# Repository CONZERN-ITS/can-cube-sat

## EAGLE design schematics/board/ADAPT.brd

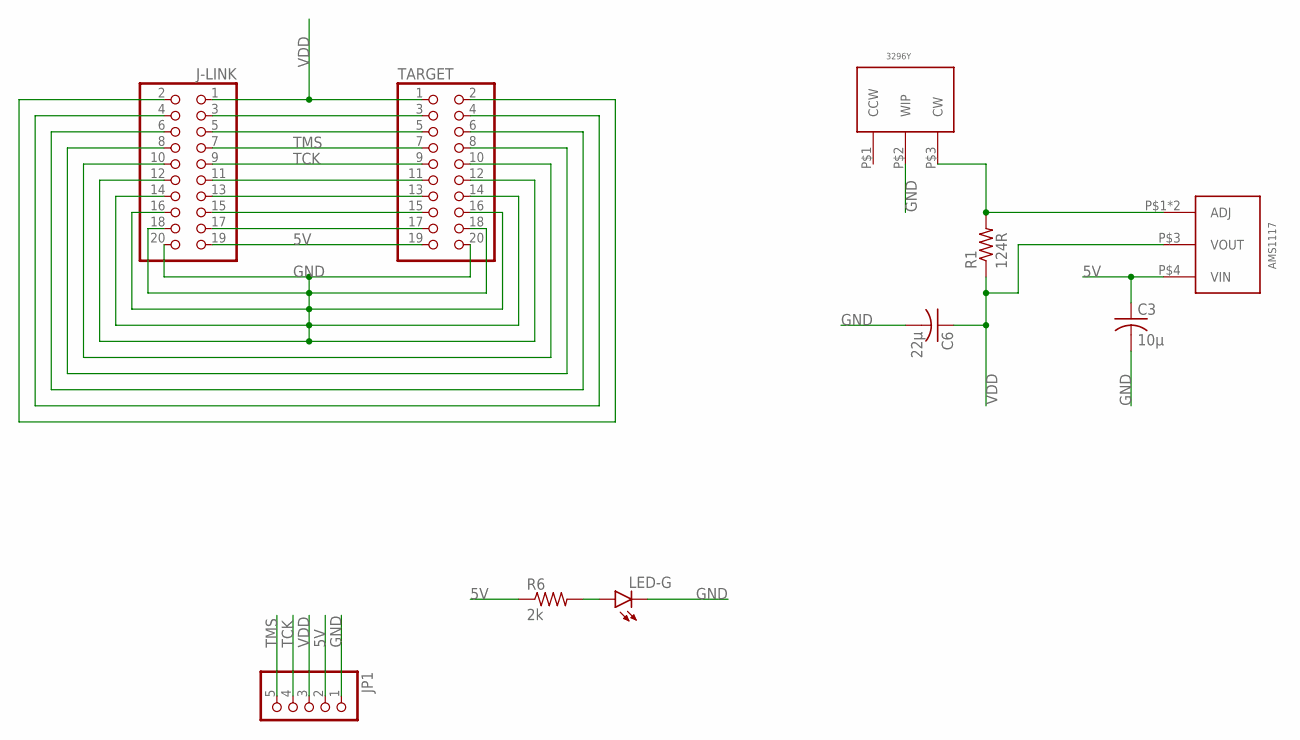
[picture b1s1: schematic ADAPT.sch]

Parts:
3296Y: 3296Y
AMS1117: AMS1117
C3: 10µ; C1206
C6: 22µ; C1206
J-LINK: PINHD-2X10; 2X10
JP1: PINHD-1X5; 1X05
LED-G: LEDCHIPLED_0603; CHIPLED_0603
R1: 124R; R0805
R6: 2k; R0603
TARGET: PINHD-2X10; 2X10

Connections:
5V: AMS1117.P$4 (VIN), C3.1, J-LINK.19, JP1.2, R6.1, TARGET.19
GND: 3296Y.P$2 (WIP), C3.2, C6.2, J-LINK.12, J-LINK.14, J-LINK.16, J-LINK.18, J-LINK.20, JP1.1, LED-G.C, TARGET.12, TARGET.14, TARGET.16, TARGET.18, TARGET.20
unnamed: J-LINK.3, TARGET.3
unnamed: J-LINK.5, TARGET.5
unnamed: 3296Y.P$3 (CW), AMS1117.P$1 (ADJ), AMS1117.P$2 (ADJ), R1.2
unnamed: J-LINK.11, TARGET.11
unnamed: J-LINK.13, TARGET.13
unnamed: J-LINK.15, TARGET.15
unnamed: J-LINK.17, TARGET.17
unnamed: J-LINK.10, TARGET.10
unnamed: J-LINK.8, TARGET.8
unnamed: J-LINK.6, TARGET.6
unnamed: J-LINK.4, TARGET.4
unnamed: J-LINK.2, TARGET.2
unnamed: LED-G.A, R6.2
TCK: J-LINK.9, JP1.4, TARGET.9
TMS: J-LINK.7, JP1.5, TARGET.7
VDD: AMS1117.P$3 (VOUT), C6.1, J-LINK.1, JP1.3, R1.1, TARGET.1

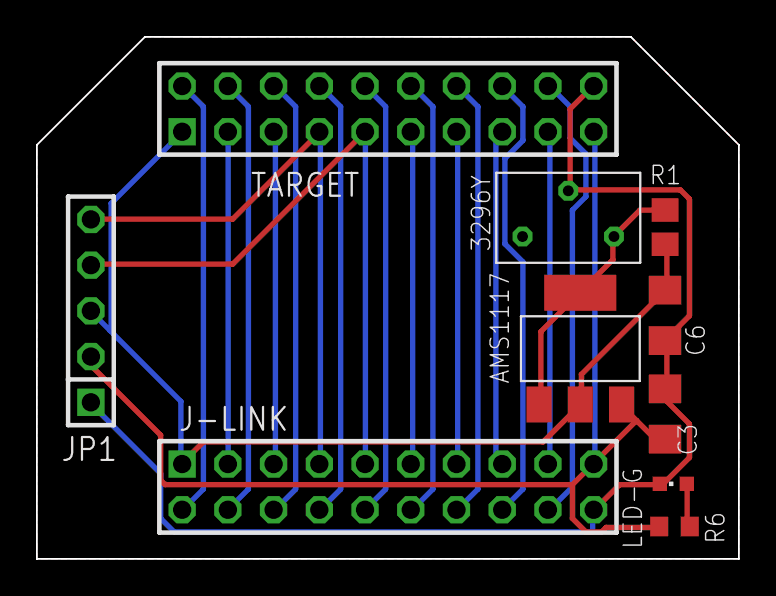
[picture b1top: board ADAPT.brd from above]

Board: 2 copper layers, 39.0 x 29.0 mm, 10 parts (0 on the bottom side), 18 nets.

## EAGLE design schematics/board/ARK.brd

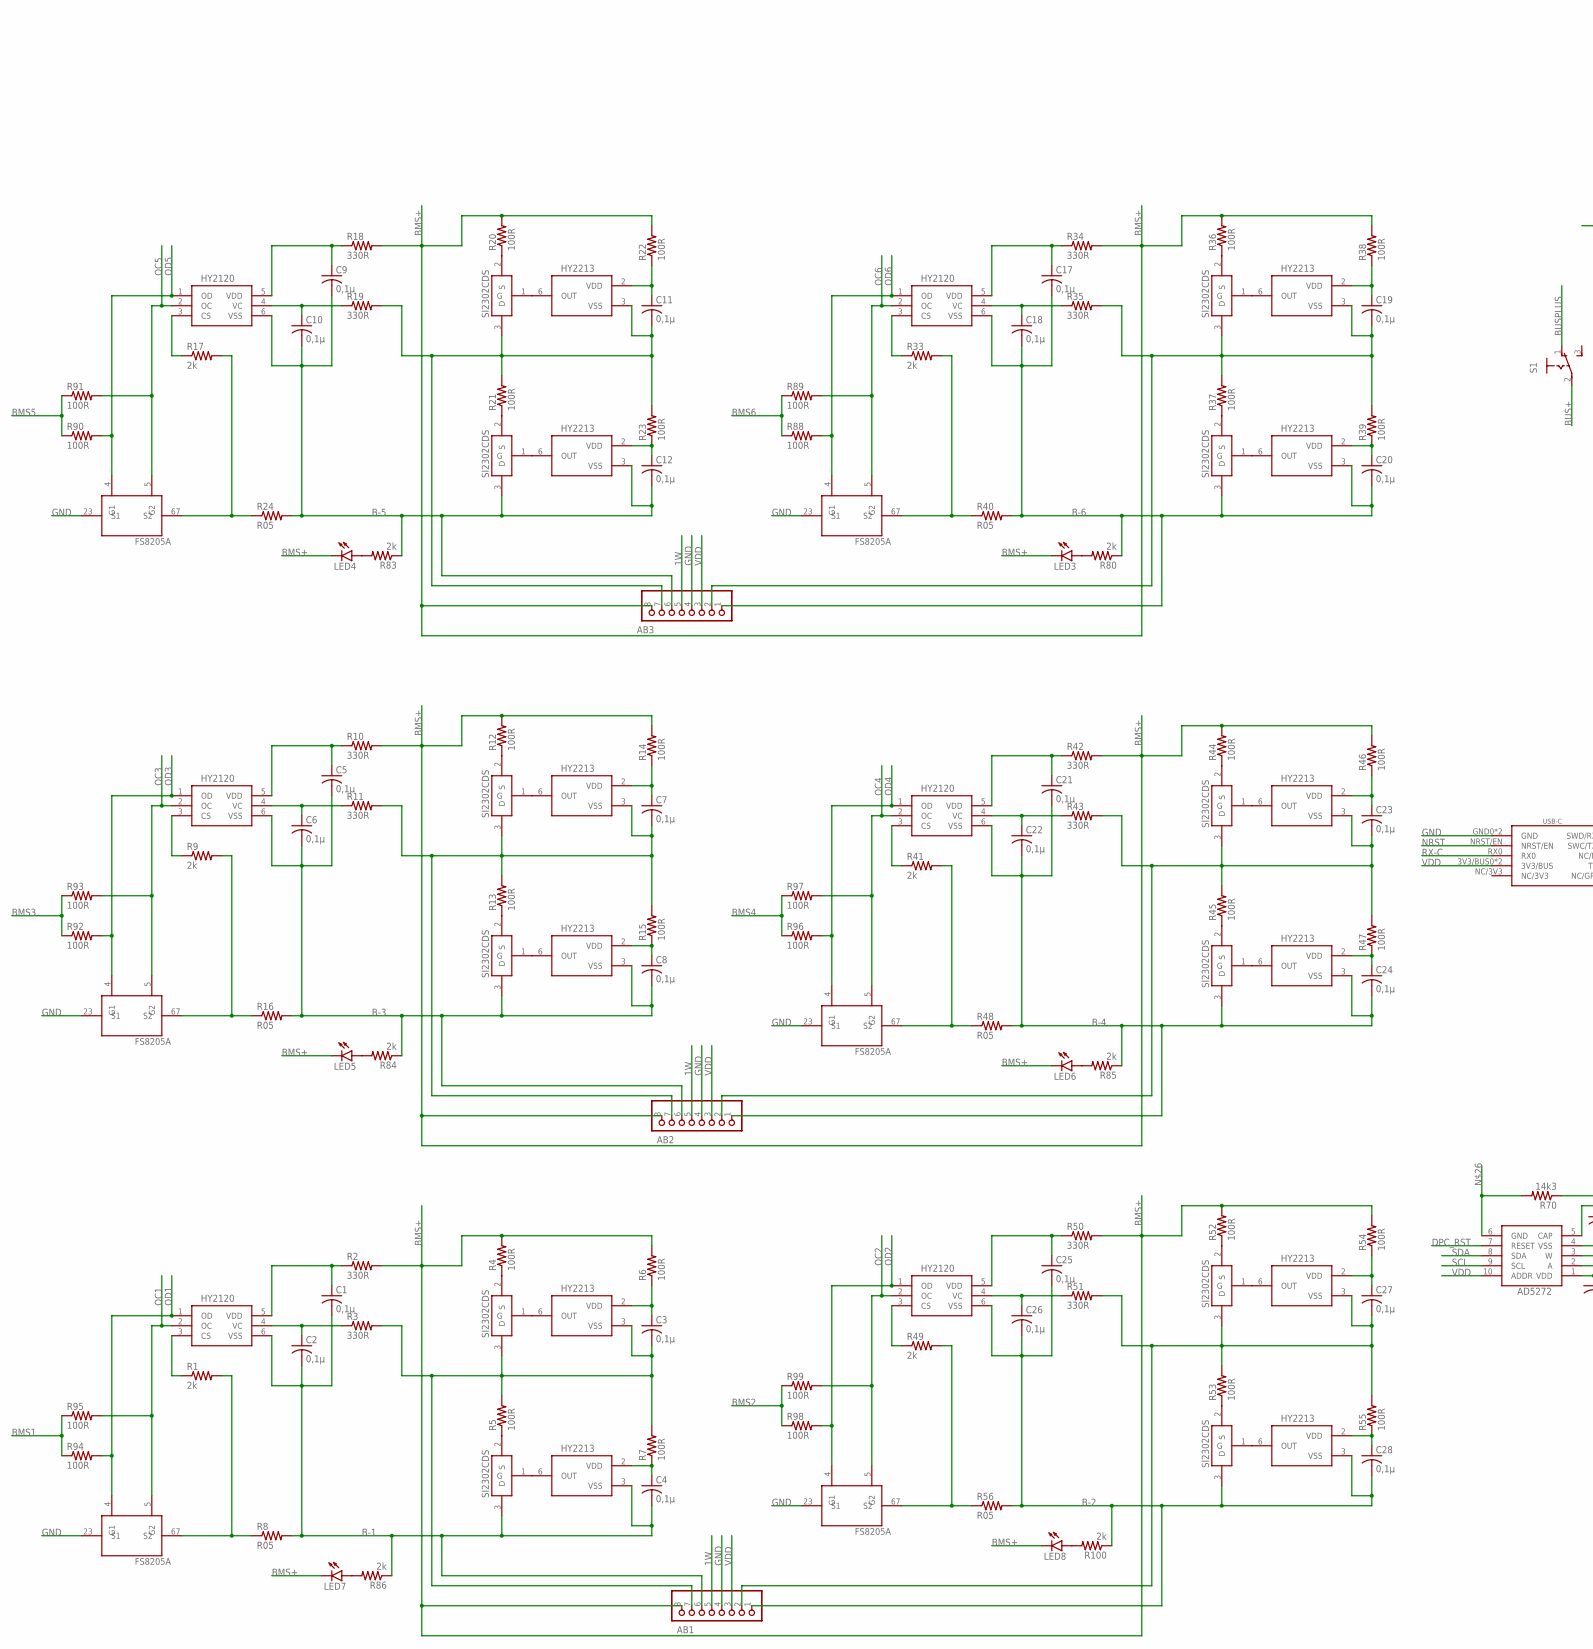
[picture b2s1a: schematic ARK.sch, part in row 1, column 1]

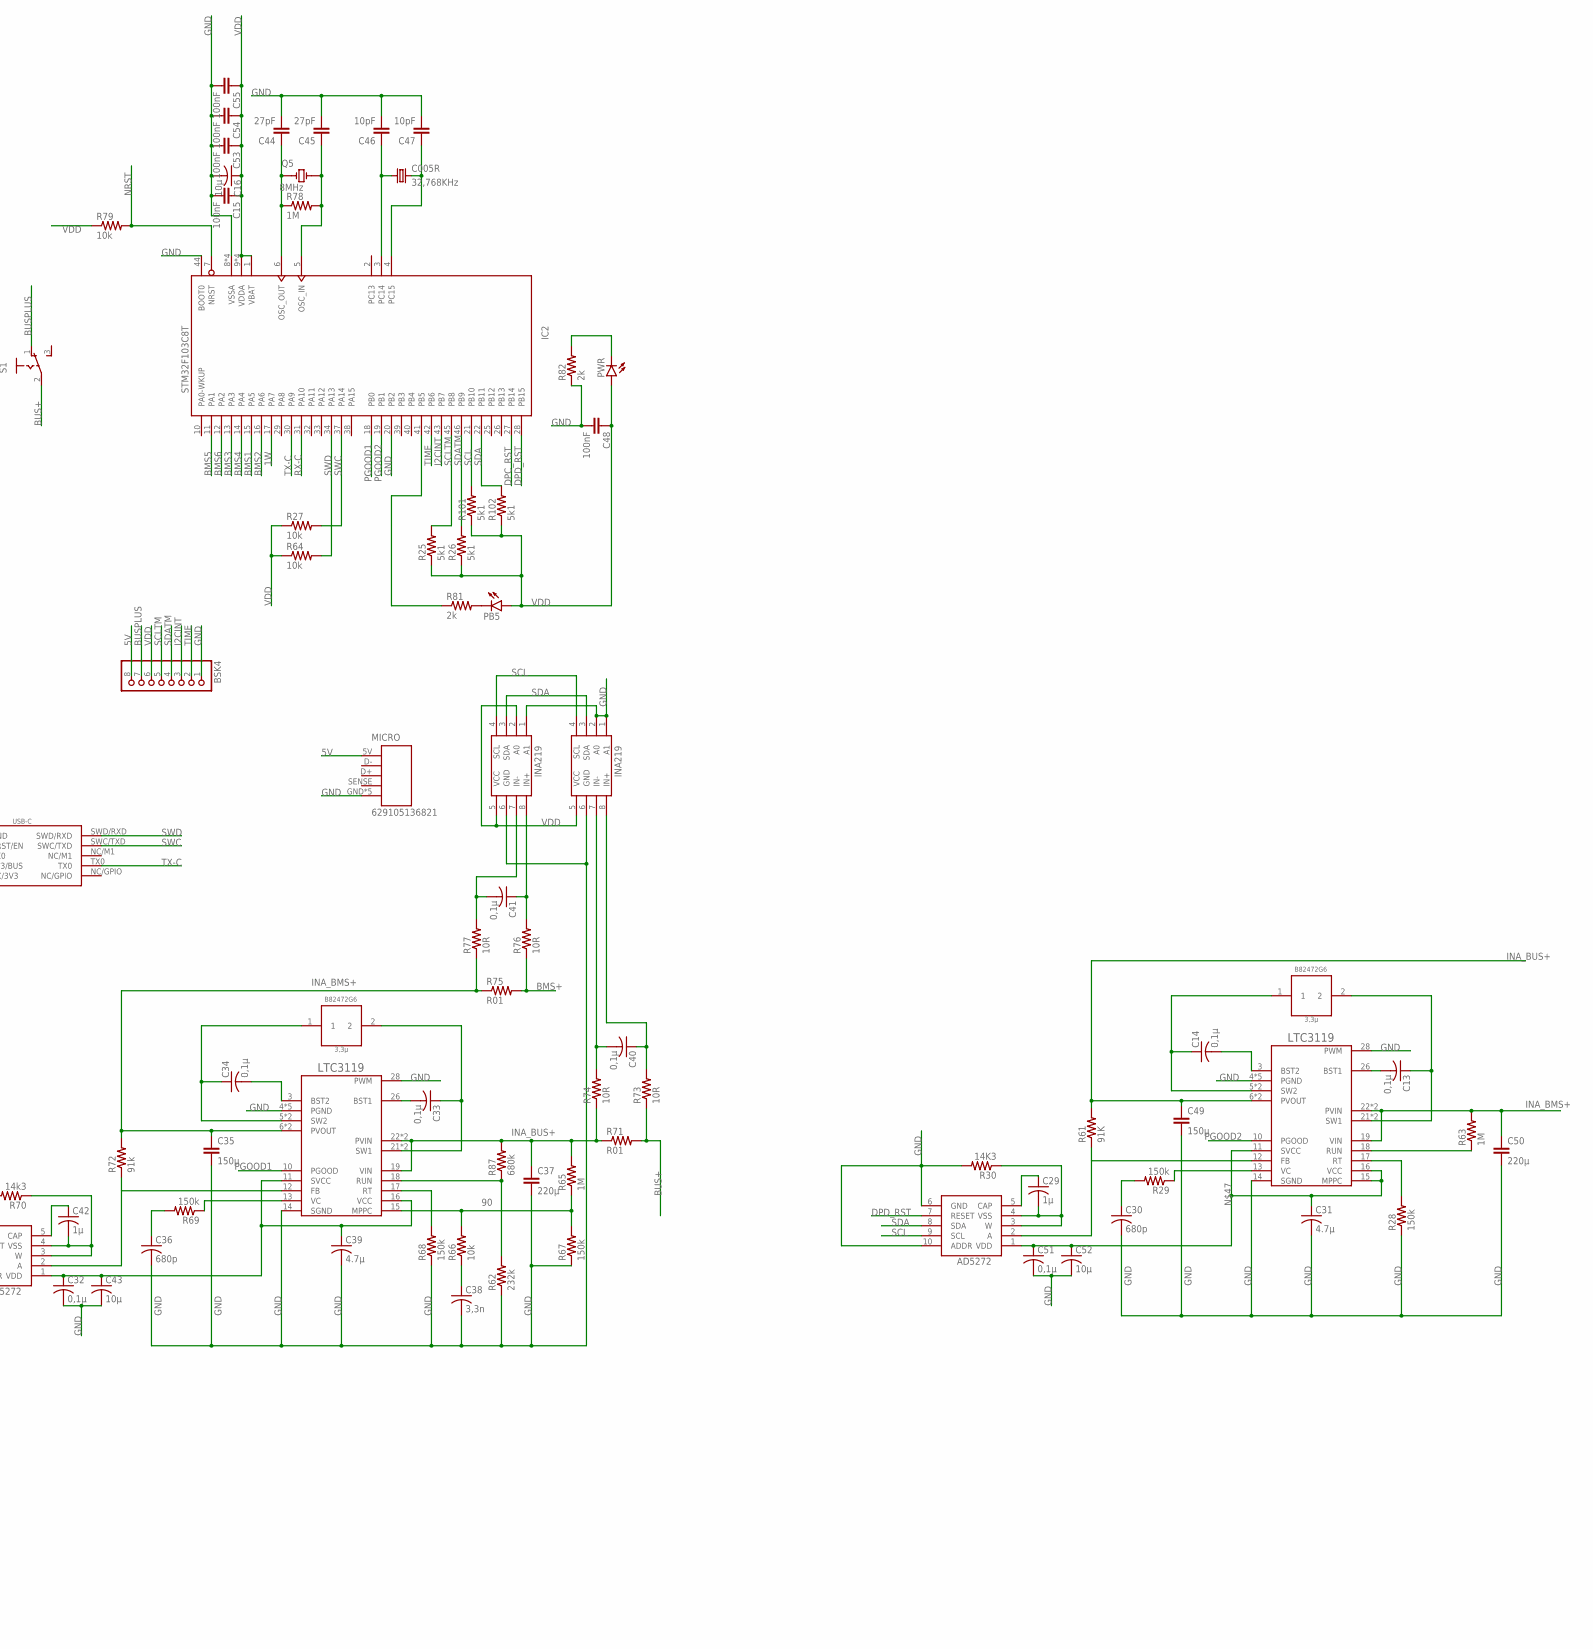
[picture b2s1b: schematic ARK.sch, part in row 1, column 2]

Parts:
3,3µH, 3,3µH1: 3,3µ; B82472G6
AB1, AB2, AB3: PINHD-1X8; 1X08
AD5272#2: AD5272
BSK4: PINHD-1X8; 1X08
C1, C2, C3, C4, C5, C6, C7, C8, C9, C10, C11, C12, C13, C14, C17, C18, C19, C20, C21, C22, C23, C24, C25, C26, C27, C28, C32, C33, C34, C40, C41, C51: 0,1µ; C0603
C005R: 32,768KHz; C005R
C15, C48, C53, C54, C55: 100nF; C0603
C16, C43, C52: 10µ; C1206
C29, C42: 1µ; C0603
C30, C36: 680p; C0603
C31, C39: 4.7µ; C1206
C35, C49: 150µ; ECAP150
C37, C50: 220µ; ECAP220
C38: 3,3n; C0603
C44, C45: 27pF; C0603
C46, C47: 10pF; C0603
IC2: STM32F103C8T; LQFP48
INA219#1: INA219AID
LED3, LED4, LED5, LED6, LED7, LED8: LEDCHIPLED_0603; CHIPLED_0603
MICRO: 629105136821
PB5: LEDCHIPLED_0603; CHIPLED_0603
PWR: LEDCHIPLED_0603; CHIPLED_0603
Q5: 8MHz; XTAL_9C-8.000MEEJ-T
R1, R9, R17, R33, R41, R49, R80, R81, R82, R83, R84, R85, R86, R100: 2k; R0603
R2, R3, R10, R11, R18, R19, R34, R35, R42, R43, R50, R51: 330R; R0603
R4, R5, R6, R7, R12, R13, R14, R15, R20, R21, R22, R23, R36, R37, R38, R39, R44, R45, R46, R47, R52, R53, R54, R55, R88, R89, R90, R91, R92, R93, R94, R95, R96, R97, R98, R99: 100R; R0603
R8, R16, R24, R40, R48, R56: R05; R2512
R25, R26, R101, R102: 5k1; R0603
R27, R64, R66, R79: 10k; R0603
R28, R29, R67, R68, R69: 150k; R0603
R30: 14K3; R0603
R61: 91K; R0603
R62: 232k; R0603
R63, R65, R78: 1M; R0603
R70: 14k3; R0603
R71, R75: R01; R2512
R72: 91k; R0603
R73, R74, R76, R77: 10R; R0603
R87: 680k; R0603
S1: UNICS-SWITCH
U$1, U$8, U$15, U$24, U$25, U$26: FS8205A-
U$3, U$10, U$17, U$31, U$38, U$45: HY2120
U$4, U$5, U$11, U$12, U$18, U$19, U$32, U$33, U$39, U$40, U$46, U$47: HY2213
U$6, U$7, U$13, U$14, U$20, U$21, U$34, U$35, U$41, U$42, U$48, U$49: SI2302CDS
U$16, U$59: LTC3119
U$23: USB-C
U$57: INA219AID
U$60: AD5272

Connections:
1W: AB1.5, AB2.5, AB3.5, IC2.17 (PA7)
5V: BSK4.8, MICRO.5V (1)
90: R65.1, R66.2, R67.2, U$59.15 (MPPC)
B-1: AB1.6, C1.2, C2.2, C4.2, R8.2, R86.1, U$3.6 (VSS), U$5.3 (VSS), U$7.3 (D)
B-2: AB1.1, C25.2, C26.2, C28.2, R56.2, R100.1, U$45.6 (VSS), U$47.3 (VSS), U$49.3 (D)
B-3: AB2.6, C5.2, C6.2, C8.2, R16.2, R84.1, U$10.6 (VSS), U$12.3 (VSS), U$14.3 (D)
B-4: AB2.1, C21.2, C22.2, C24.2, R48.2, R85.1, U$38.6 (VSS), U$40.3 (VSS), U$42.3 (D)
B-5: AB3.6, C9.2, C10.2, C12.2, R24.2, R83.1, U$17.6 (VSS), U$19.3 (VSS), U$21.3 (D)
B-6: AB3.1, C17.2, C18.2, C20.2, R40.2, R80.1, U$31.6 (VSS), U$33.3 (VSS), U$35.3 (D)
BMS1: IC2.15 (PA5), R94.1, R95.1
BMS2: IC2.16 (PA6), R98.1, R99.1
BMS3: IC2.13 (PA3), R92.1, R93.1
BMS4: IC2.14 (PA4), R96.1, R97.1
BMS5: IC2.11 (PA1), R90.1, R91.1
BMS6: IC2.12 (PA2), R88.1, R89.1
BMS+: AB1.8, AB2.8, AB3.8, LED3.C, LED4.C, LED5.C, LED6.C, LED7.C, LED8.C, R2.2, R4.2, R6.2, R10.2, R12.2, R14.2, R18.2, R20.2, R22.2, R34.2, R36.2, R38.2, R42.2, R44.2, R46.2, R50.2, R52.2, R54.2, R75.2, R76.1
BUS+: R71.2, R73.1, S1.2
BUSPLUS: BSK4.7, S1.1 (O)
DPC_RST: IC2.27 (PB14), U$60.7 (RESET)
DPD_RST: AD5272#2.7 (RESET), IC2.28 (PB15)
GND: AB1.4, AB2.4, AB3.4, AD5272#2.6 (GND), AD5272#2.10 (ADDR), BSK4.1, C15.2, C16.2, C30.2, C31.2, C32.2, C35.P$2 (2), C36.2, C37.P$2 (2), C38.2, C39.2, C42.2, C43.2, C44.2, C45.2, C46.2, C47.2, C48.2, C49.P$2 (2), C50.P$2 (2), C51.2, C52.2, C53.2, C54.2, C55.2, IC2.8 (VSSA), IC2.20 (PB2), IC2.23 (VSSA), IC2.35 (VSSA), IC2.44 (BOOT0), IC2.47 (VSSA), INA219#1.1 (A1), INA219#1.2 (A0), INA219#1.6 (GND), MICRO.GND (5), MICRO.Z1 (5), MICRO.Z2 (5), MICRO.Z3 (5), MICRO.Z4 (5), R28.1, R30.2, R62.1, R67.1, R68.1, R70.1, R82.1, U$1.23 (S1), U$8.23 (S1), U$15.23 (S1), U$16.4 (PGND), U$16.9 (PGND), U$16.14 (SGND), U$16.20 (PGND), U$16.25 (PGND), U$16.28 (PWM), U$16.29 (PGND), U$23.GND0 (GND), U$23.GND1 (GND), U$24.23 (S1), U$25.23 (S1), U$26.23 (S1), U$57.1 (A1), U$57.6 (GND), U$59.4 (PGND), U$59.9 (PGND), U$59.14 (SGND), U$59.20 (PGND), U$59.25 (PGND), U$59.28 (PWM), U$59.29 (PGND), U$60.3 (W), U$60.4 (VSS)
I2CINT: BSK4.3, IC2.43 (PB7)
INA_BMS+: C35.P$1 (1), C50.P$1 (1), R63.2, R72.2, R75.1, R77.1, U$16.19 (VIN), U$16.22 (PVIN), U$16.23 (PVIN), U$59.6 (PVOUT), U$59.7 (PVOUT)
INA_BUS+: C37.P$1 (1), C49.P$1 (1), R61.2, R65.2, R71.1, R74.1, R87.2, U$16.6 (PVOUT), U$16.7 (PVOUT), U$59.19 (VIN), U$59.22 (PVIN), U$59.23 (PVIN)
unnamed: C1.1, R2.1, U$3.5 (VDD)
unnamed: C4.1, R7.1, U$5.2 (VDD)
unnamed: R1.1, U$3.3 (CS)
unnamed: C3.1, R6.1, U$4.2 (VDD)
unnamed: AD5272#2.2 (A), R61.1, U$16.12 (FB)
unnamed: U$4.6 (OUT), U$6.1 (G)
unnamed: R4.1, U$6.2 (S)
unnamed: AB1.7, C3.2, R3.2, R5.2, R7.2, U$4.3 (VSS), U$6.3 (D)
unnamed: U$5.6 (OUT), U$7.1 (G)
unnamed: R5.1, U$7.2 (S)
unnamed: 3,3µH1.2, C13.1, U$16.21 (SW1), U$16.24 (SW1)
unnamed: 3,3µH1.1, C14.1, U$16.5 (SW2), U$16.8 (SW2)
unnamed: R1.2, R8.1, U$26.67 (S2)
unnamed: C2.1, R3.1, U$3.4 (VC)
unnamed: C5.1, R10.1, U$10.5 (VDD)
unnamed: PB5.C, R81.2
unnamed: R9.1, U$10.3 (CS)
unnamed: C7.1, R14.1, U$11.2 (VDD)
unnamed: U$11.6 (OUT), U$13.1 (G)
unnamed: R12.1, U$13.2 (S)
unnamed: U$12.6 (OUT), U$14.1 (G)
unnamed: R13.1, U$14.2 (S)
unnamed: R9.2, R16.1, U$25.67 (S2)
unnamed: R72.1, U$59.12 (FB), U$60.2 (A)
unnamed: R70.2, U$60.6 (GND)
unnamed: C6.1, R11.1, U$10.4 (VC)
unnamed: C8.1, R15.1, U$12.2 (VDD)
unnamed: R28.2, U$16.17 (RT)
unnamed: AB2.7, C7.2, R11.2, R13.2, R15.2, U$11.3 (VSS), U$13.3 (D)
unnamed: C13.2, U$16.26 (BST1)
unnamed: C9.1, R18.1, U$17.5 (VDD)
unnamed: R17.1, U$17.3 (CS)
unnamed: C11.1, R22.1, U$18.2 (VDD)
unnamed: U$18.6 (OUT), U$20.1 (G)
unnamed: R20.1, U$20.2 (S)
unnamed: U$19.6 (OUT), U$21.1 (G)
unnamed: R21.1, U$21.2 (S)
unnamed: R17.2, R24.1, U$24.67 (S2)
unnamed: R29.1, U$16.13 (VC)
unnamed: C30.1, R29.2
unnamed: C10.1, R19.1, U$17.4 (VC)
unnamed: C12.1, R23.1, U$19.2 (VDD)
unnamed: C32.1, C39.1, C43.1, U$59.11 (SVCC), U$59.16 (VCC), U$60.1 (VDD)
unnamed: AB3.7, C11.2, R19.2, R21.2, R23.2, U$18.3 (VSS), U$20.3 (D)
unnamed: AD5272#2.1 (VDD), C31.1, C51.1, C52.1, U$16.11 (SVCC), U$16.15 (MPPC), U$16.16 (VCC)
unnamed: AD5272#2.3 (W), AD5272#2.4 (VSS), C29.2, R30.1
unnamed: AD5272#2.5 (CAP), C29.1
unnamed: C14.2, U$16.3 (BST2)
unnamed: R63.1, U$16.18 (RUN)
unnamed: LED3.A, R80.2
unnamed: R62.2, R87.1, U$59.18 (RUN)
unnamed: LED4.A, R83.2
unnamed: LED5.A, R84.2
unnamed: LED6.A, R85.2
unnamed: LED7.A, R86.2
unnamed: LED8.A, R100.2
unnamed: C17.1, R34.1, U$31.5 (VDD)
unnamed: R33.1, U$31.3 (CS)
unnamed: C19.1, R38.1, U$32.2 (VDD)
unnamed: U$32.6 (OUT), U$34.1 (G)
unnamed: R36.1, U$34.2 (S)
unnamed: U$33.6 (OUT), U$35.1 (G)
unnamed: R37.1, U$35.2 (S)
unnamed: R33.2, R40.1, U$15.67 (S2)
unnamed: C18.1, R35.1, U$31.4 (VC)
unnamed: C20.1, R39.1, U$33.2 (VDD)
unnamed: AB3.2, C19.2, R35.2, R37.2, R39.2, U$32.3 (VSS), U$34.3 (D)
unnamed: C21.1, R42.1, U$38.5 (VDD)
unnamed: R41.1, U$38.3 (CS)
unnamed: C23.1, R46.1, U$39.2 (VDD)
unnamed: U$39.6 (OUT), U$41.1 (G)
unnamed: R44.1, U$41.2 (S)
unnamed: U$40.6 (OUT), U$42.1 (G)
unnamed: R45.1, U$42.2 (S)
unnamed: R41.2, R48.1, U$8.67 (S2)
unnamed: C22.1, R43.1, U$38.4 (VC)
unnamed: C24.1, R47.1, U$40.2 (VDD)
unnamed: AB2.2, C23.2, R43.2, R45.2, R47.2, U$39.3 (VSS), U$41.3 (D)
unnamed: C25.1, R50.1, U$45.5 (VDD)
unnamed: R49.1, U$45.3 (CS)
unnamed: C27.1, R54.1, U$46.2 (VDD)
unnamed: U$46.6 (OUT), U$48.1 (G)
unnamed: R52.1, U$48.2 (S)
unnamed: U$47.6 (OUT), U$49.1 (G)
unnamed: R53.1, U$49.2 (S)
unnamed: R49.2, R56.1, U$1.67 (S2)
unnamed: C26.1, R51.1, U$45.4 (VC)
unnamed: C28.1, R55.1, U$47.2 (VDD)
unnamed: AB1.2, C27.2, R51.2, R53.2, R55.2, U$46.3 (VSS), U$48.3 (D)
unnamed: C34.2, U$59.3 (BST2)
unnamed: 3,3µH.2, C33.1, U$59.21 (SW1), U$59.24 (SW1)
unnamed: 3,3µH.1, C34.1, U$59.5 (SW2), U$59.8 (SW2)
unnamed: C44.1, IC2.6 (OSC_OUT), Q5.1, R78.1
unnamed: R69.1, U$59.13 (VC)
unnamed: C36.1, R69.2
unnamed: C38.1, R66.1
unnamed: C40.2, INA219#1.7 (IN-), R74.2
unnamed: R68.2, U$59.17 (RT)
unnamed: C33.2, U$59.26 (BST1)
unnamed: C45.1, IC2.5 (OSC_IN), Q5.2, R78.2
unnamed: C40.1, INA219#1.8 (IN+), R73.2
unnamed: C005R.P$2 (2), C47.1, IC2.4 (PC15)
unnamed: C41.1, R76.2, U$57.8 (IN+)
unnamed: C41.2, R77.2, U$57.7 (IN-)
unnamed: C005R.P$1 (1), C46.1, IC2.3 (PC14)
unnamed: C42.1, U$60.5 (CAP)
unnamed: PWR.C, R82.2
unnamed: IC2.41 (PB5), R81.1
NRST: IC2.7 (NRST), R79.2, U$23.NRST/EN
OC1: R95.2, U$3.2 (OC), U$26.5 (G2)
OC2: R99.2, U$1.5 (G2), U$45.2 (OC)
OC3: R93.2, U$10.2 (OC), U$25.5 (G2)
OC4: R97.2, U$8.5 (G2), U$38.2 (OC)
OC5: R91.2, U$17.2 (OC), U$24.5 (G2)
OC6: R89.2, U$15.5 (G2), U$31.2 (OC)
OD1: R94.2, U$3.1 (OD), U$26.4 (G1)
OD2: R98.2, U$1.4 (G1), U$45.1 (OD)
OD3: R92.2, U$10.1 (OD), U$25.4 (G1)
OD4: R96.2, U$8.4 (G1), U$38.1 (OD)
OD5: R90.2, U$17.1 (OD), U$24.4 (G1)
OD6: R88.2, U$15.4 (G1), U$31.1 (OD)
PGOOD1: IC2.18 (PB0), U$59.10 (PGOOD)
PGOOD2: IC2.19 (PB1), U$16.10 (PGOOD)
RX-C: IC2.31 (PA10), U$23.RX0
SCL: AD5272#2.9 (SCL), IC2.21 (PB10), INA219#1.4 (SCL), R101.2, U$57.4 (SCL), U$60.9 (SCL)
SCLTM: BSK4.5, IC2.45 (PB8), R25.2
SDA: AD5272#2.8 (SDA), IC2.22 (PB11), INA219#1.3 (SDA), R102.2, U$57.3 (SDA), U$60.8 (SDA)
SDATM: BSK4.4, IC2.46 (PB9), R26.2
SWC: IC2.37 (PA14), R27.2, U$23.SWC/TXD
SWD: IC2.34 (PA13), R64.2, U$23.SWD/RXD
TIME: BSK4.2, IC2.42 (PB6)
TX-C: IC2.30 (PA9), U$23.TX0
VDD: AB1.3, AB2.3, AB3.3, BSK4.6, C15.1, C16.1, C48.1, C53.1, C54.1, C55.1, IC2.1 (VBAT), IC2.9 (VDDA), IC2.24 (VDDA), IC2.36 (VDDA), IC2.48 (VDDA), INA219#1.5 (VCC), PB5.A, PWR.A, R25.1, R26.1, R27.1, R64.1, R79.1, R101.1, R102.1, U$23.3V3/BUS0 (3V3/BUS), U$23.3V3/BUS1 (3V3/BUS), U$57.2 (A0), U$57.5 (VCC), U$60.10 (ADDR)

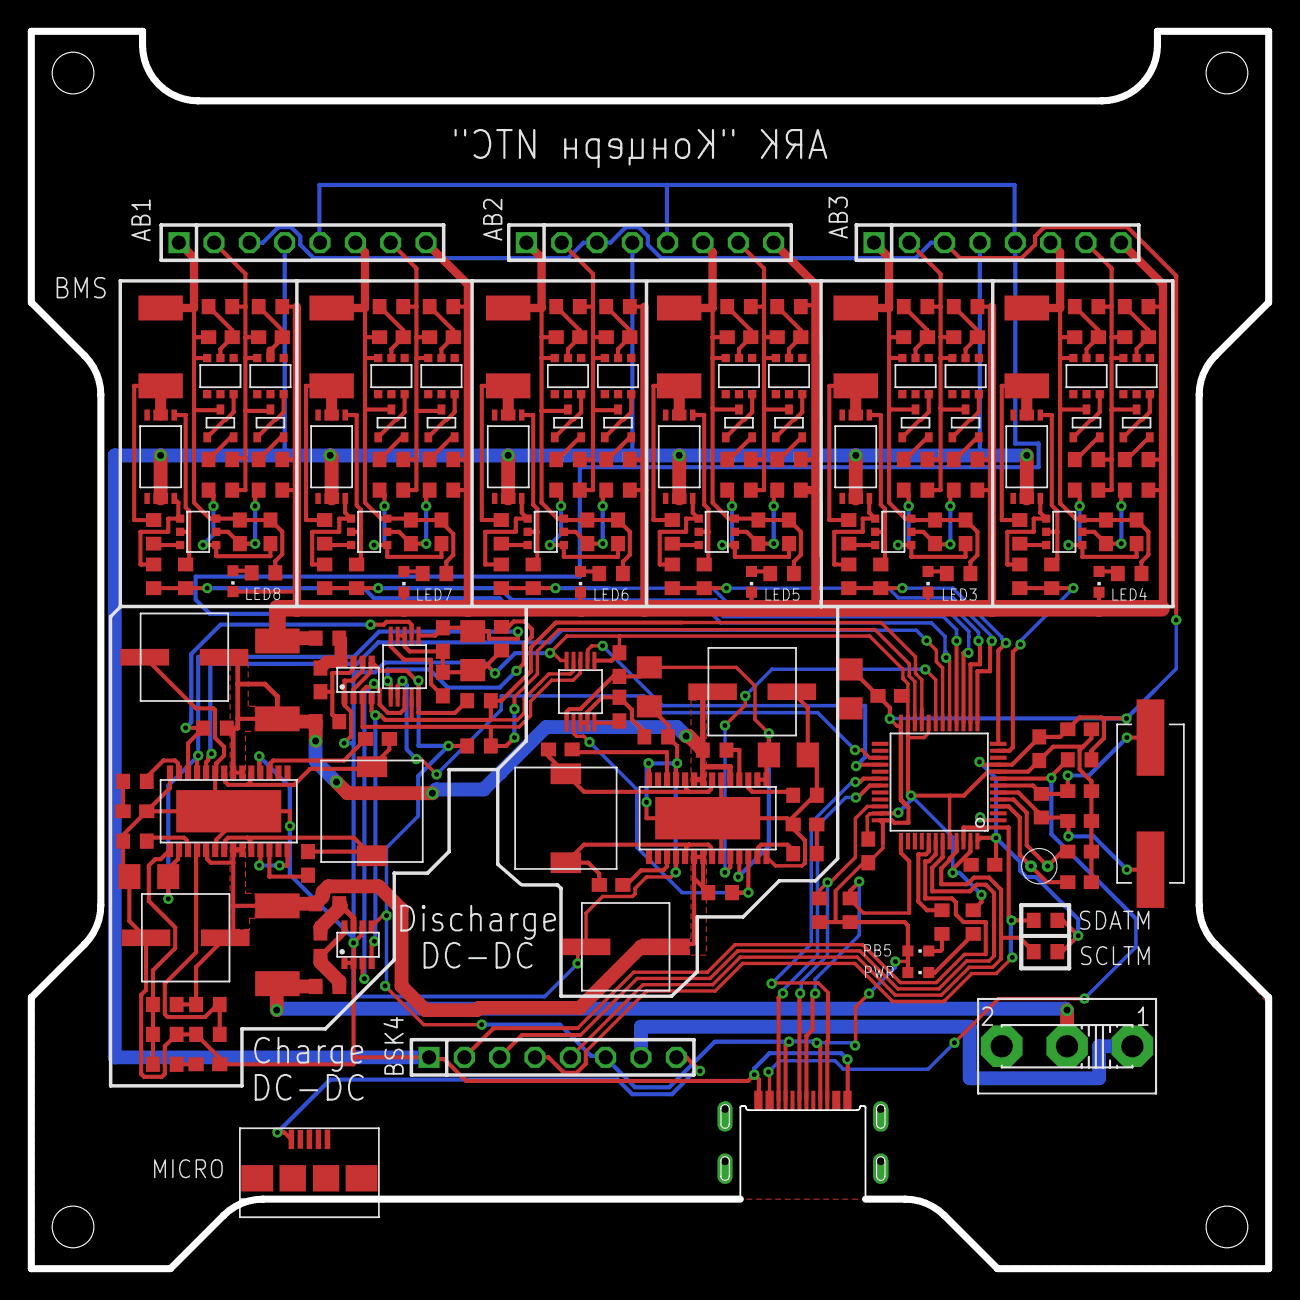
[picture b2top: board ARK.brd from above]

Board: 2 copper layers, 89.0 x 89.0 mm, 213 parts (0 on the bottom side), 157 nets.

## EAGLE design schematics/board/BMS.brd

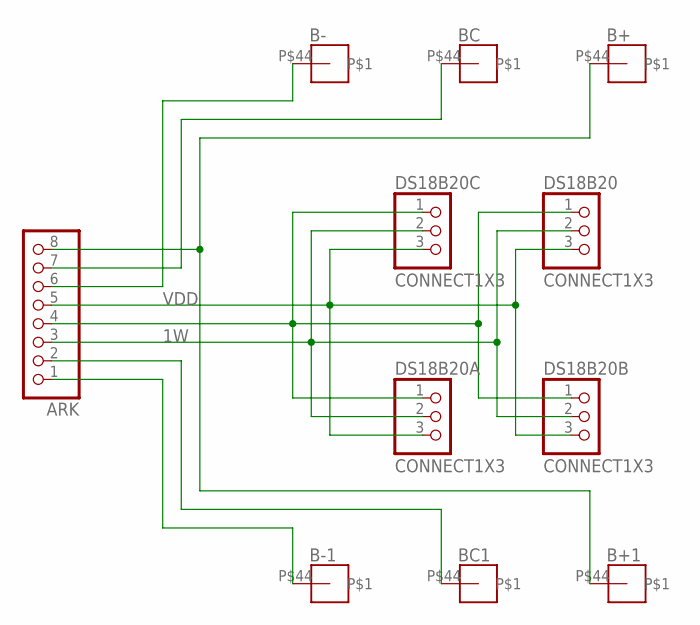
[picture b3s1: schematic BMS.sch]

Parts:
ARK: PINHD-1X8; 1X08
B+, B+1: DRILLBAT5
B-, B-1: DRILLBAT5
BC, BC1: DRILLBAT5
DS18B20, DS18B20A, DS18B20B, DS18B20C: CONNECT1X3

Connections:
1W: ARK.3, DS18B20.2, DS18B20A.2, DS18B20B.2, DS18B20C.2
BMS+: ARK.8, B+.P$44, B+1.P$44
unnamed: ARK.4, DS18B20.1, DS18B20A.1, DS18B20B.1, DS18B20C.1
unnamed: ARK.6, B-.P$44
unnamed: ARK.1, B-1.P$44
unnamed: ARK.7, BC.P$44
unnamed: ARK.2, BC1.P$44
VDD: ARK.5, DS18B20.3, DS18B20A.3, DS18B20B.3, DS18B20C.3

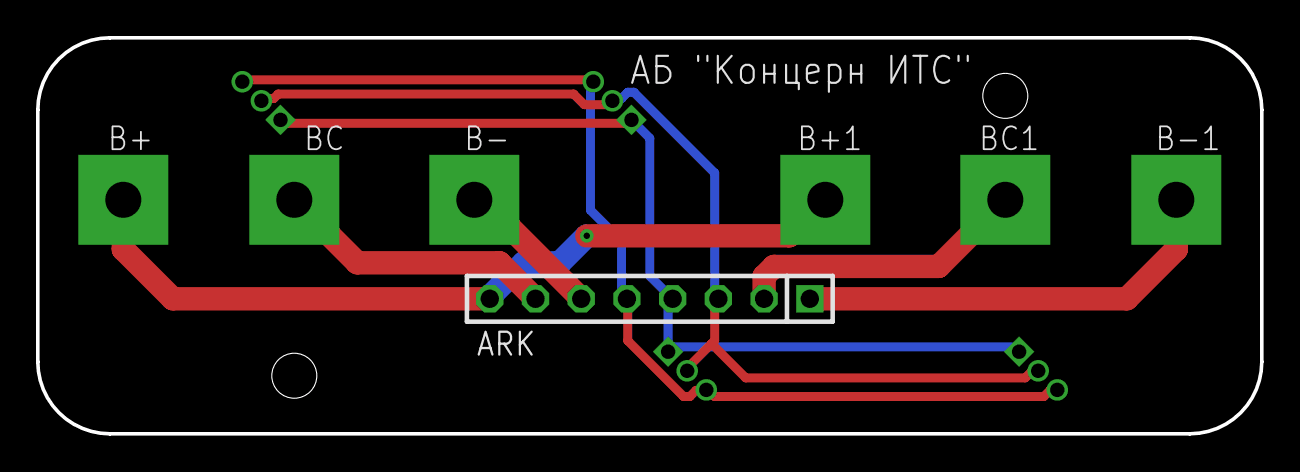
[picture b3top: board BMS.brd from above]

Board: 2 copper layers, 68.0 x 22.0 mm, 11 parts (0 on the bottom side), 8 nets.

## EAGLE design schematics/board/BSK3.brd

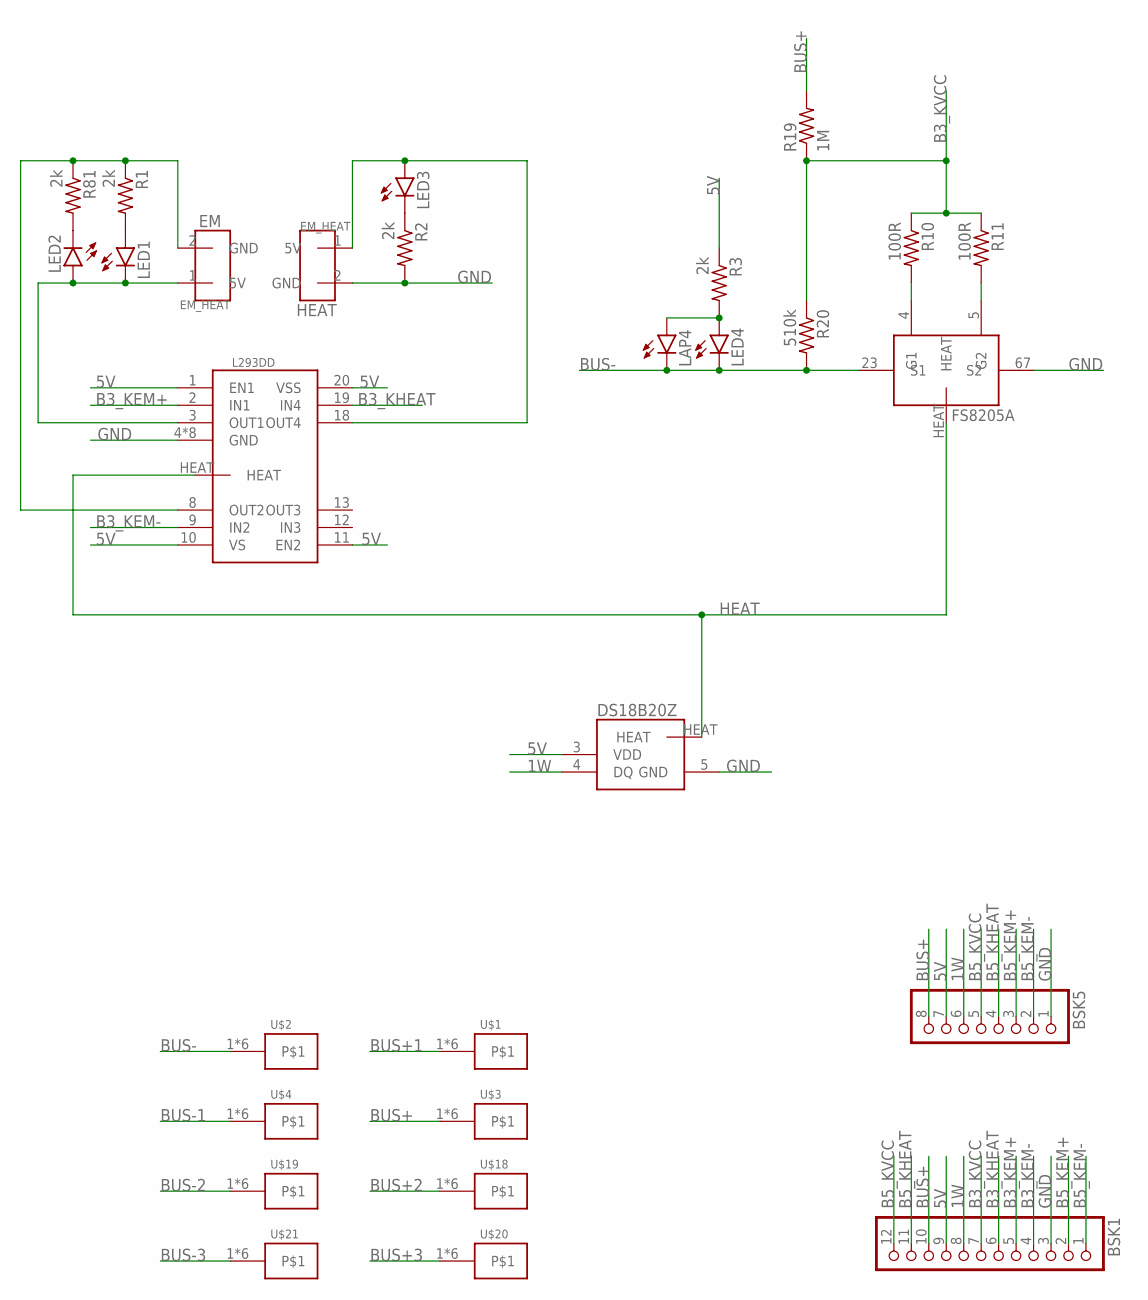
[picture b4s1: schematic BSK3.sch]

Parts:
BSK1: PINHD-1X12; 1X12
BSK5: PINHD-1X8; 1X08
DS18B20Z: DS18B20Z
FS8205A: FS8205A+
L293DD: L293DD
LAP4: LAP4-BOTTOM; P47F-BOTTOM
LED1, LED2, LED3, LED4: LEDCHIPLED_0603; CHIPLED_0603
R1, R2, R3, R81: 2k; R0603
R10, R11: 100R; R0603
R19: 1M; R0603
R20: 510k; R0603
U$1, U$2, U$3, U$4, U$18, U$19, U$20, U$21: KCONNECT
U$6, U$7: EM_HEAT

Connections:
1W: BSK1.8, BSK5.6, DS18B20Z.4 (DQ)
5V: BSK1.9, BSK5.7, DS18B20Z.3 (VDD), L293DD.1 (EN1), L293DD.10 (VS), L293DD.11 (EN2), L293DD.20 (VSS), R3.1
B3_KEM+: BSK1.5, L293DD.2 (IN1)
B3_KEM-: BSK1.4, L293DD.9 (IN2)
B3_KHEAT: BSK1.6, L293DD.19 (IN4)
B3_KVCC: BSK1.7, R10.1, R11.1, R19.1, R20.1
B5_KEM+: BSK1.2, BSK5.3
B5_KEM-: BSK1.1, BSK5.2
B5_KHEAT: BSK1.11, BSK5.4
B5_KVCC: BSK1.12, BSK5.5
BUS+: BSK1.10, BSK5.8, R19.2, U$3.1, U$3.2, U$3.3, U$3.4, U$3.P$1, U$3.P$2
BUS+1: U$1.1, U$1.2, U$1.3, U$1.4, U$1.P$1, U$1.P$2
BUS+2: U$18.1, U$18.2, U$18.3, U$18.4, U$18.P$1, U$18.P$2
BUS+3: U$20.1, U$20.2, U$20.3, U$20.4, U$20.P$1, U$20.P$2
BUS-: FS8205A.23 (S1), LAP4.C, LED4.C, R20.2, U$2.1, U$2.2, U$2.3, U$2.4, U$2.P$1, U$2.P$2
BUS-1: U$4.1, U$4.2, U$4.3, U$4.4, U$4.P$1, U$4.P$2
BUS-2: U$19.1, U$19.2, U$19.3, U$19.4, U$19.P$1, U$19.P$2
BUS-3: U$21.1, U$21.2, U$21.3, U$21.4, U$21.P$1, U$21.P$2
GND: BSK1.3, BSK5.1, DS18B20Z.5 (GND), FS8205A.67 (S2), L293DD.4 (GND), L293DD.5 (GND), L293DD.6 (GND), L293DD.7 (GND), L293DD.14 (GND), L293DD.15 (GND), L293DD.16 (GND), L293DD.17 (GND), R2.2, U$7.2 (GND)
HEAT: DS18B20Z.HEAT, FS8205A.HEAT, L293DD.HEAT
unnamed: L293DD.3 (OUT1), LED1.C, LED2.A, U$6.1 (5V)
unnamed: L293DD.8 (OUT2), R1.1, R81.1, U$6.2 (GND)
unnamed: L293DD.18 (OUT4), LED3.A, U$7.1 (5V)
unnamed: LED2.C, R81.2
unnamed: LED1.A, R1.2
unnamed: LED3.C, R2.1
unnamed: LAP4.A, LED4.A, R3.2
unnamed: FS8205A.4 (G1), R10.2
unnamed: FS8205A.5 (G2), R11.2

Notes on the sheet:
HEAT

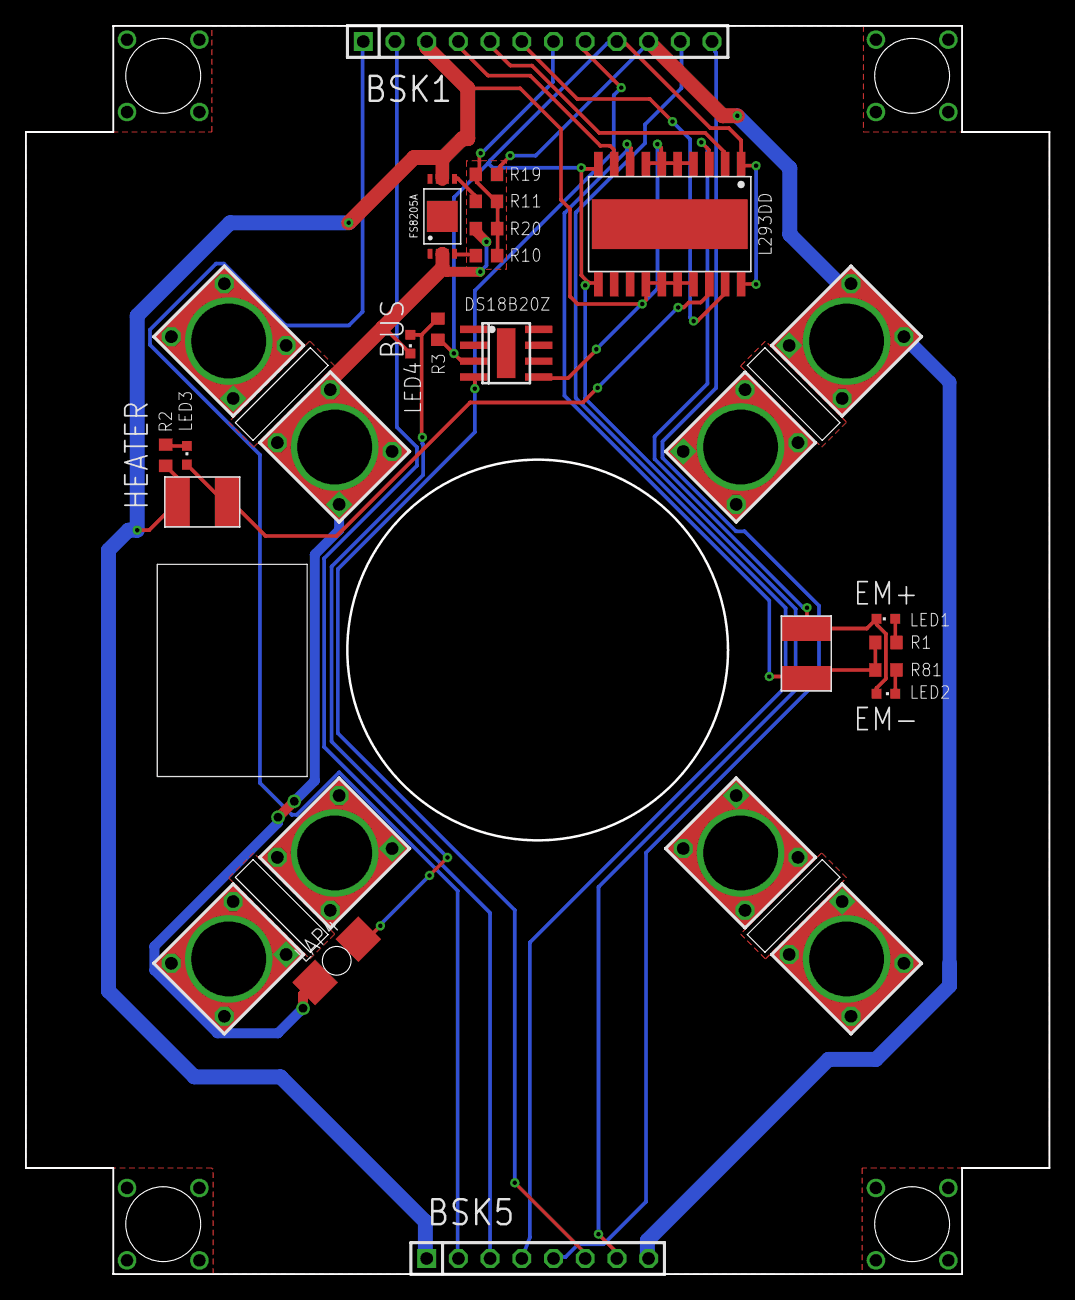
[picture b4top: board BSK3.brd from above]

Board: 2 copper layers, 82.0 x 100.0 mm, 28 parts (0 on the bottom side), 29 nets.

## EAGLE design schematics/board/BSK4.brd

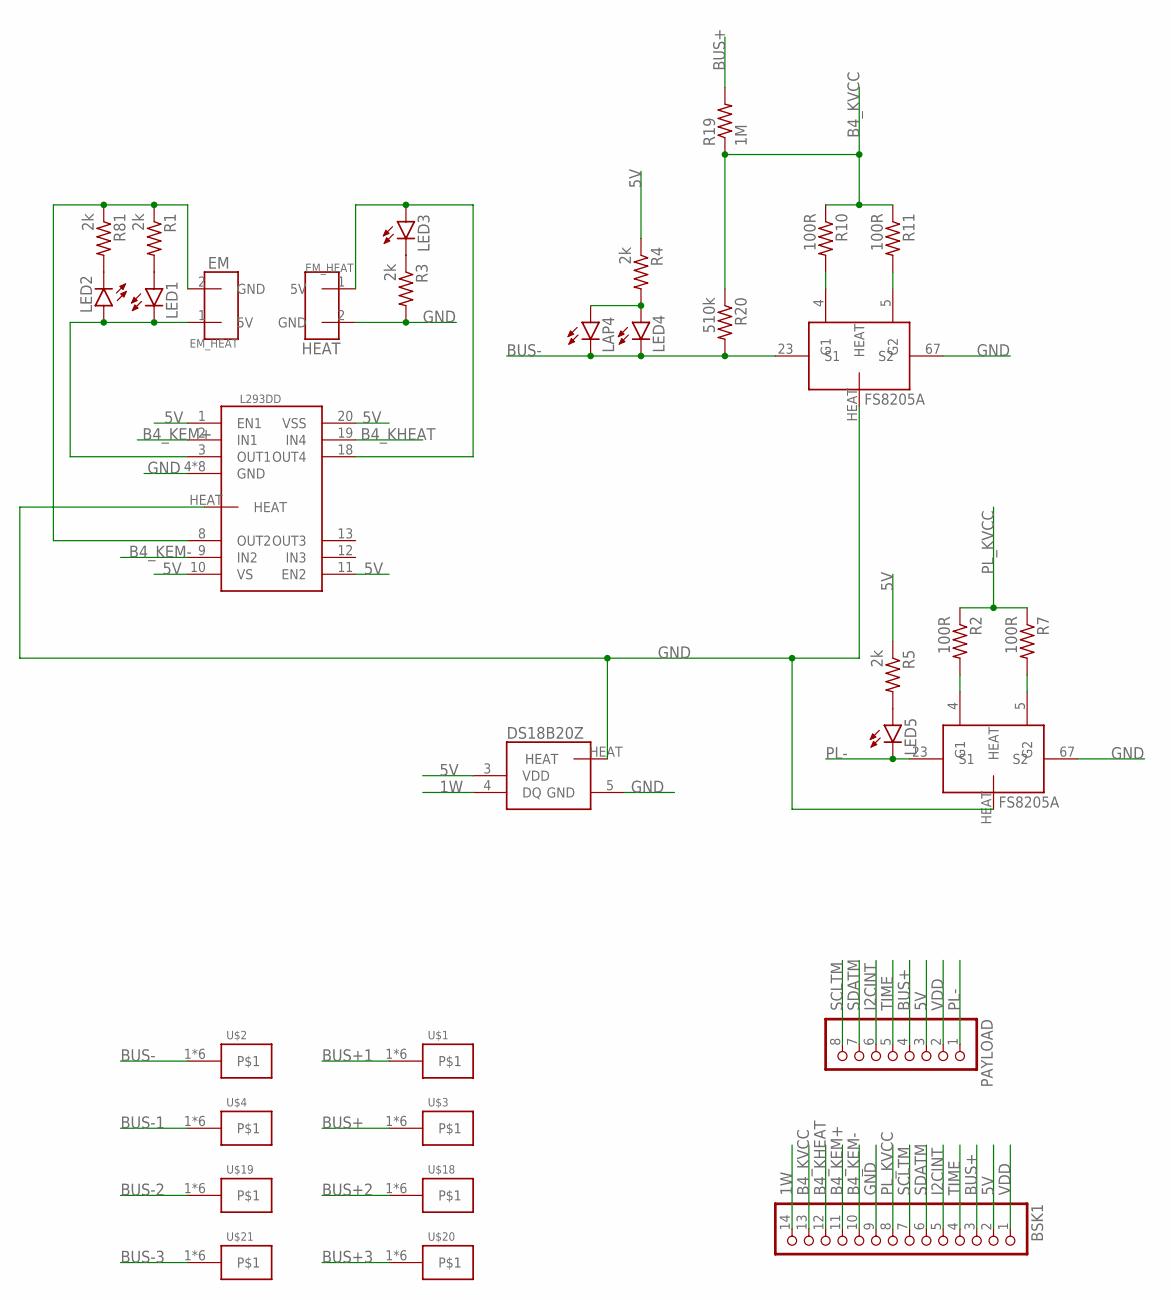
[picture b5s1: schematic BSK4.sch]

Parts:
BSK1: PINHD-1X14; 1X14
DS18B20Z: DS18B20Z
FS8205A#1, FS8205A#2: FS8205A+
L293DD: L293DD
LAP4: LAP4-BOTTOM; P47F-BOTTOM
LED1, LED2, LED3, LED4, LED5: LEDCHIPLED_0603; CHIPLED_0603
PAYLOAD: PINHD-1X8; 1X08
R1, R3, R4, R5, R81: 2k; R0603
R2, R7, R10, R11: 100R; R0603
R19: 1M; R0603
R20: 510k; R0603
U$1, U$2, U$3, U$4, U$18, U$19, U$20, U$21: KCONNECT
U$6, U$7: EM_HEAT

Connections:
1W: BSK1.14, DS18B20Z.4 (DQ)
5V: BSK1.2, DS18B20Z.3 (VDD), L293DD.1 (EN1), L293DD.10 (VS), L293DD.11 (EN2), L293DD.20 (VSS), PAYLOAD.3, R4.1, R5.1
B4_KEM+: BSK1.11, L293DD.2 (IN1)
B4_KEM-: BSK1.10, L293DD.9 (IN2)
B4_KHEAT: BSK1.12, L293DD.19 (IN4)
B4_KVCC: BSK1.13, R10.1, R11.1, R19.1, R20.1
BUS+: BSK1.3, PAYLOAD.4, R19.2, U$3.1, U$3.2, U$3.3, U$3.4, U$3.P$1, U$3.P$2
BUS+1: U$1.1, U$1.2, U$1.3, U$1.4, U$1.P$1, U$1.P$2
BUS+2: U$18.1, U$18.2, U$18.3, U$18.4, U$18.P$1, U$18.P$2
BUS+3: U$20.1, U$20.2, U$20.3, U$20.4, U$20.P$1, U$20.P$2
BUS-: FS8205A#1.23 (S1), LAP4.C, LED4.C, R20.2, U$2.1, U$2.2, U$2.3, U$2.4, U$2.P$1, U$2.P$2
BUS-1: U$4.1, U$4.2, U$4.3, U$4.4, U$4.P$1, U$4.P$2
BUS-2: U$19.1, U$19.2, U$19.3, U$19.4, U$19.P$1, U$19.P$2
BUS-3: U$21.1, U$21.2, U$21.3, U$21.4, U$21.P$1, U$21.P$2
GND: BSK1.9, DS18B20Z.5 (GND), DS18B20Z.HEAT, FS8205A#1.67 (S2), FS8205A#1.HEAT, FS8205A#2.67 (S2), FS8205A#2.HEAT, L293DD.4 (GND), L293DD.5 (GND), L293DD.6 (GND), L293DD.7 (GND), L293DD.14 (GND), L293DD.15 (GND), L293DD.16 (GND), L293DD.17 (GND), L293DD.HEAT, R3.2, U$7.2 (GND)
I2CINT: BSK1.5, PAYLOAD.6
unnamed: L293DD.3 (OUT1), LED1.C, LED2.A, U$6.1 (5V)
unnamed: L293DD.8 (OUT2), R1.1, R81.1, U$6.2 (GND)
unnamed: L293DD.18 (OUT4), LED3.A, U$7.1 (5V)
unnamed: FS8205A#2.4 (G1), R2.2
unnamed: LED2.C, R81.2
unnamed: FS8205A#2.5 (G2), R7.2
unnamed: LED1.A, R1.2
unnamed: FS8205A#1.4 (G1), R10.2
unnamed: FS8205A#1.5 (G2), R11.2
unnamed: LED3.C, R3.1
unnamed: LAP4.A, LED4.A, R4.2
unnamed: LED5.A, R5.2
PL-: FS8205A#2.23 (S1), LED5.C, PAYLOAD.1
PL_KVCC: BSK1.8, R2.1, R7.1
SCLTM: BSK1.7, PAYLOAD.8
SDATM: BSK1.6, PAYLOAD.7
TIME: BSK1.4, PAYLOAD.5
VDD: BSK1.1, PAYLOAD.2

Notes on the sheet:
HEAT

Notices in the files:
parts and their libraries:
MicroUSB: Copyright: Würth Elektronik
